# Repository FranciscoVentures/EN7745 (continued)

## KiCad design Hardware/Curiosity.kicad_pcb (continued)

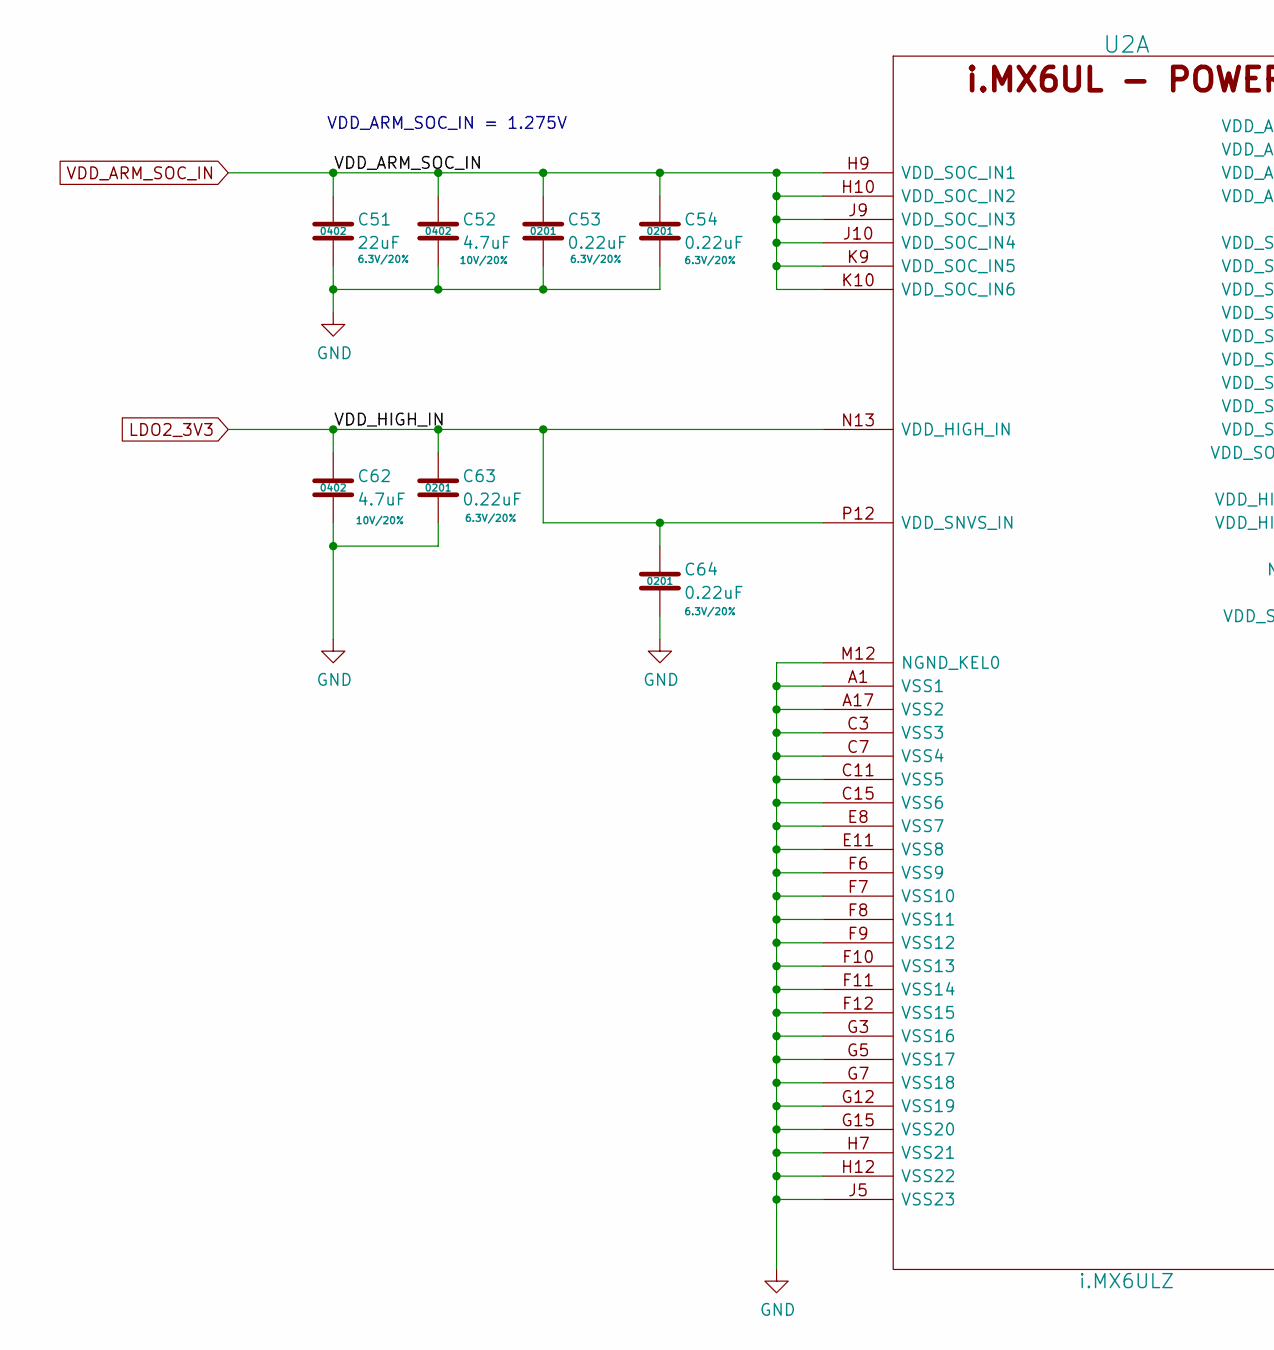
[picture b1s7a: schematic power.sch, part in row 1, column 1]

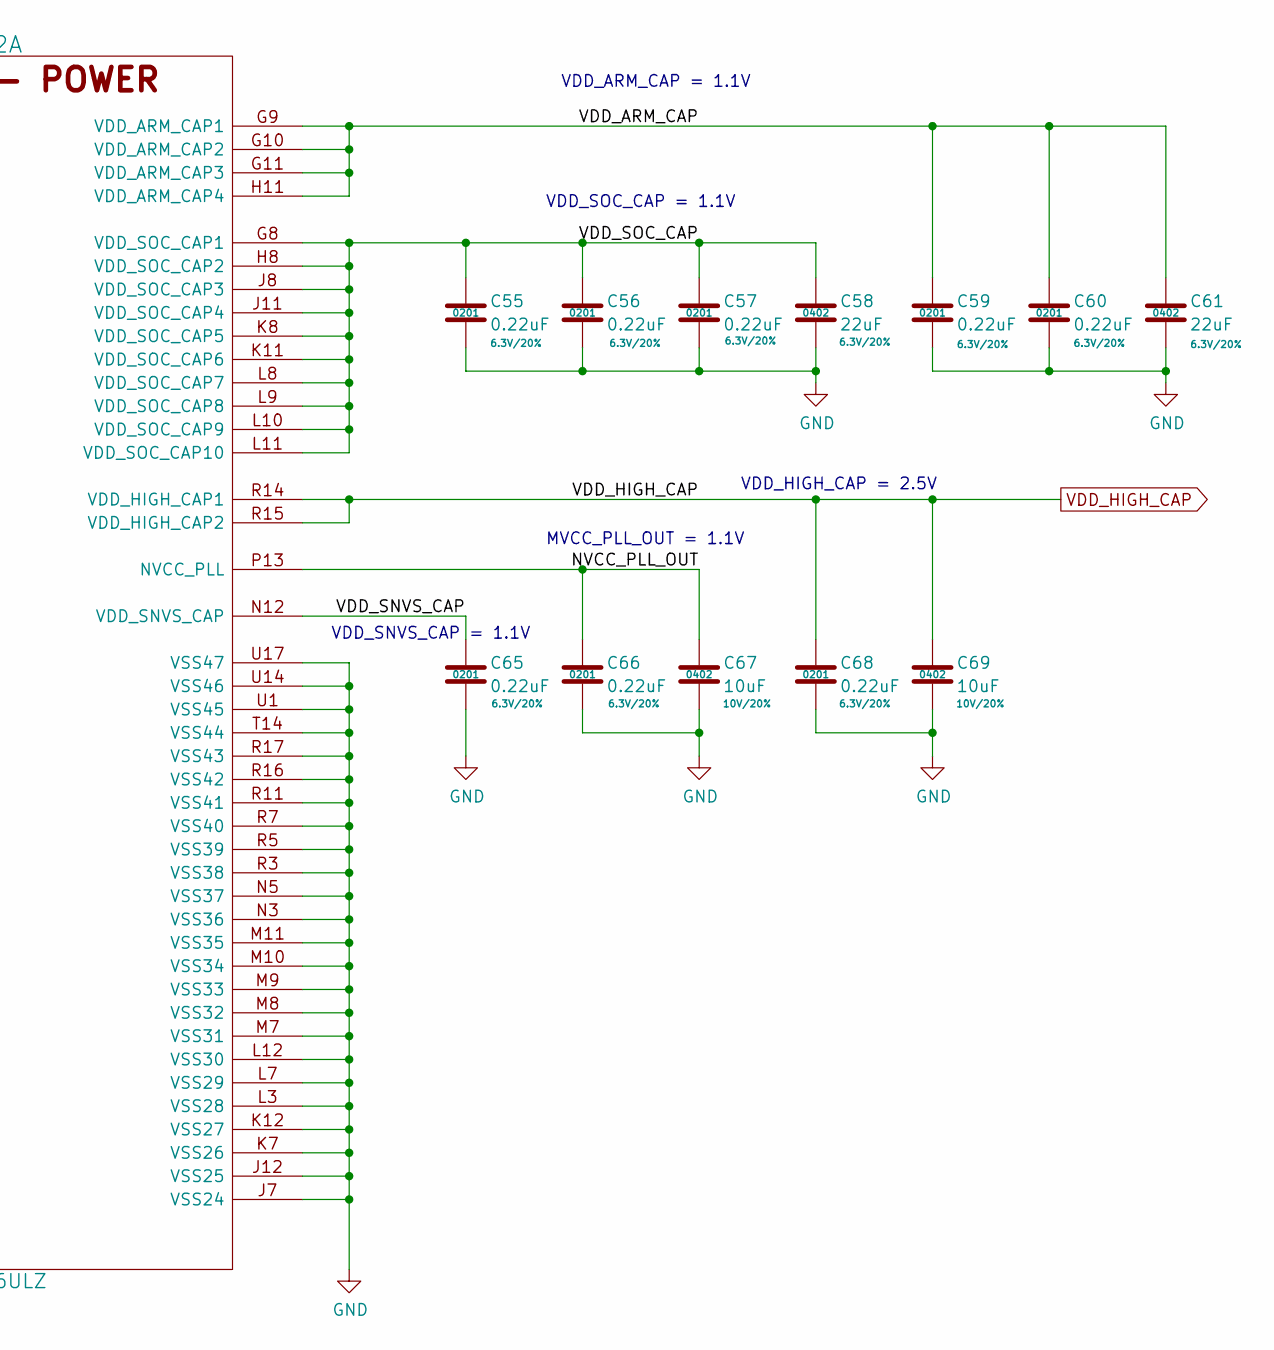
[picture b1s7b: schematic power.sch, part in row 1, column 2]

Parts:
C51, C58, C61: 22uF; SM0402; Rating 6.3V/20%; Mfg PN CL05A226MQ5N6J8; Digi-Key_PN 1276-7090-1-ND
C52, C62: 4.7uF; SM0402; Rating 10V/20%; Mfg PN ZRB15XR61A475ME01D; Digi-Key_PN 490-10984-1-ND
C53, C54, C55, C56, C57, C59, C60, C63, C64, C65, C66, C68: 0.22uF; SM0201; Rating 6.3V/20%; Mfg PN GRM033R60J224ME15D; Digi-Key_PN 490-10407-1-ND
C67, C69: 10uF; SM0402; Rating 10V/20%; Mfg PN CL05A106MP8NUB8; Digi-Key_PN 1276-6830-1-ND
U2: i.MX6ULZ; SOT1534-2; Mfg PN MCIMX6Z0DVM09AB; Digi-Key_PN 568-14726-ND

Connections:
/Power/NVCC_PLL_OUT: C66.1, C67.1, U2.P13 (NVCC_PLL); also elsewhere on the board
/Power/VDD_ARM_CAP: C59.1, C60.1, C61.1, U2.G9 (VDD_ARM_CAP1), U2.G10 (VDD_ARM_CAP2), U2.G11 (VDD_ARM_CAP3), U2.H11 (VDD_ARM_CAP4); also elsewhere on the board
/Power/VDD_SNVS_CAP: C65.1, U2.N12 (VDD_SNVS_CAP); also elsewhere on the board
/Power/VDD_SOC_CAP: C55.1, C56.1, C57.1, C58.1, U2.G8 (VDD_SOC_CAP1), U2.H8 (VDD_SOC_CAP2), U2.J8 (VDD_SOC_CAP3), U2.J11 (VDD_SOC_CAP4), U2.K8 (VDD_SOC_CAP5), U2.K11 (VDD_SOC_CAP6), U2.L8 (VDD_SOC_CAP7), U2.L9 (VDD_SOC_CAP8), U2.L10 (VDD_SOC_CAP9), U2.L11 (VDD_SOC_CAP10); also elsewhere on the board
GND: C51.2, C52.2, C53.2, C54.2, C55.2, C56.2, C57.2, C58.2, C59.2, C60.2, C61.2, C62.2, C63.2, C64.2, C65.2, C66.2, C67.2, C68.2, C69.2, U2.A1 (VSS1), U2.A17 (VSS2), U2.C3 (VSS3), U2.C7 (VSS4), U2.C11 (VSS5), U2.C15 (VSS6), U2.E8 (VSS7), U2.E11 (VSS8), U2.F6 (VSS9), U2.F7 (VSS10), U2.F8 (VSS11), U2.F9 (VSS12), U2.F10 (VSS13), U2.F11 (VSS14), U2.F12 (VSS15), U2.G3 (VSS16), U2.G5 (VSS17), U2.G7 (VSS18), U2.G12 (VSS19), U2.G15 (VSS20), U2.H7 (VSS21), U2.H12 (VSS22), U2.J5 (VSS23), U2.J7 (VSS24), U2.J12 (VSS25), U2.K7 (VSS26), U2.K12 (VSS27), U2.L3 (VSS28), U2.L7 (VSS29), U2.L12 (VSS30), U2.M7 (VSS31), U2.M8 (VSS32), U2.M9 (VSS33), U2.M10 (VSS34), U2.M11 (VSS35), U2.M12 (NGND_KEL0), U2.N3 (VSS36), U2.N5 (VSS37), U2.R3 (VSS38), U2.R5 (VSS39), U2.R7 (VSS40), U2.R11 (VSS41), U2.R16 (VSS42), U2.R17 (VSS43), U2.T14 (VSS44), U2.U1 (VSS45), U2.U14 (VSS46), U2.U17 (VSS47); also elsewhere on the board
LDO2_3V3: C62.1, C63.1, C64.1, U2.N13 (VDD_HIGH_IN), U2.P12 (VDD_SNVS_IN); also elsewhere on the board
VDD_ARM_SOC_IN: C51.1, C52.1, C53.1, C54.1, U2.H9 (VDD_SOC_IN1), U2.H10 (VDD_SOC_IN2), U2.J9 (VDD_SOC_IN3), U2.J10 (VDD_SOC_IN4), U2.K9 (VDD_SOC_IN5), U2.K10 (VDD_SOC_IN6); also elsewhere on the board
VDD_HIGH_CAP: C68.1, C69.1, U2.R14 (VDD_HIGH_CAP1), U2.R15 (VDD_HIGH_CAP2); also elsewhere on the board

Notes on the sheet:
VDD_ARM_SOC_IN = 1.275V
VDD_ARM_CAP = 1.1V
VDD_SOC_CAP = 1.1V
VDD_HIGH_CAP = 2.5V
MVCC_PLL_OUT = 1.1V
VDD_SNVS_CAP = 1.1V

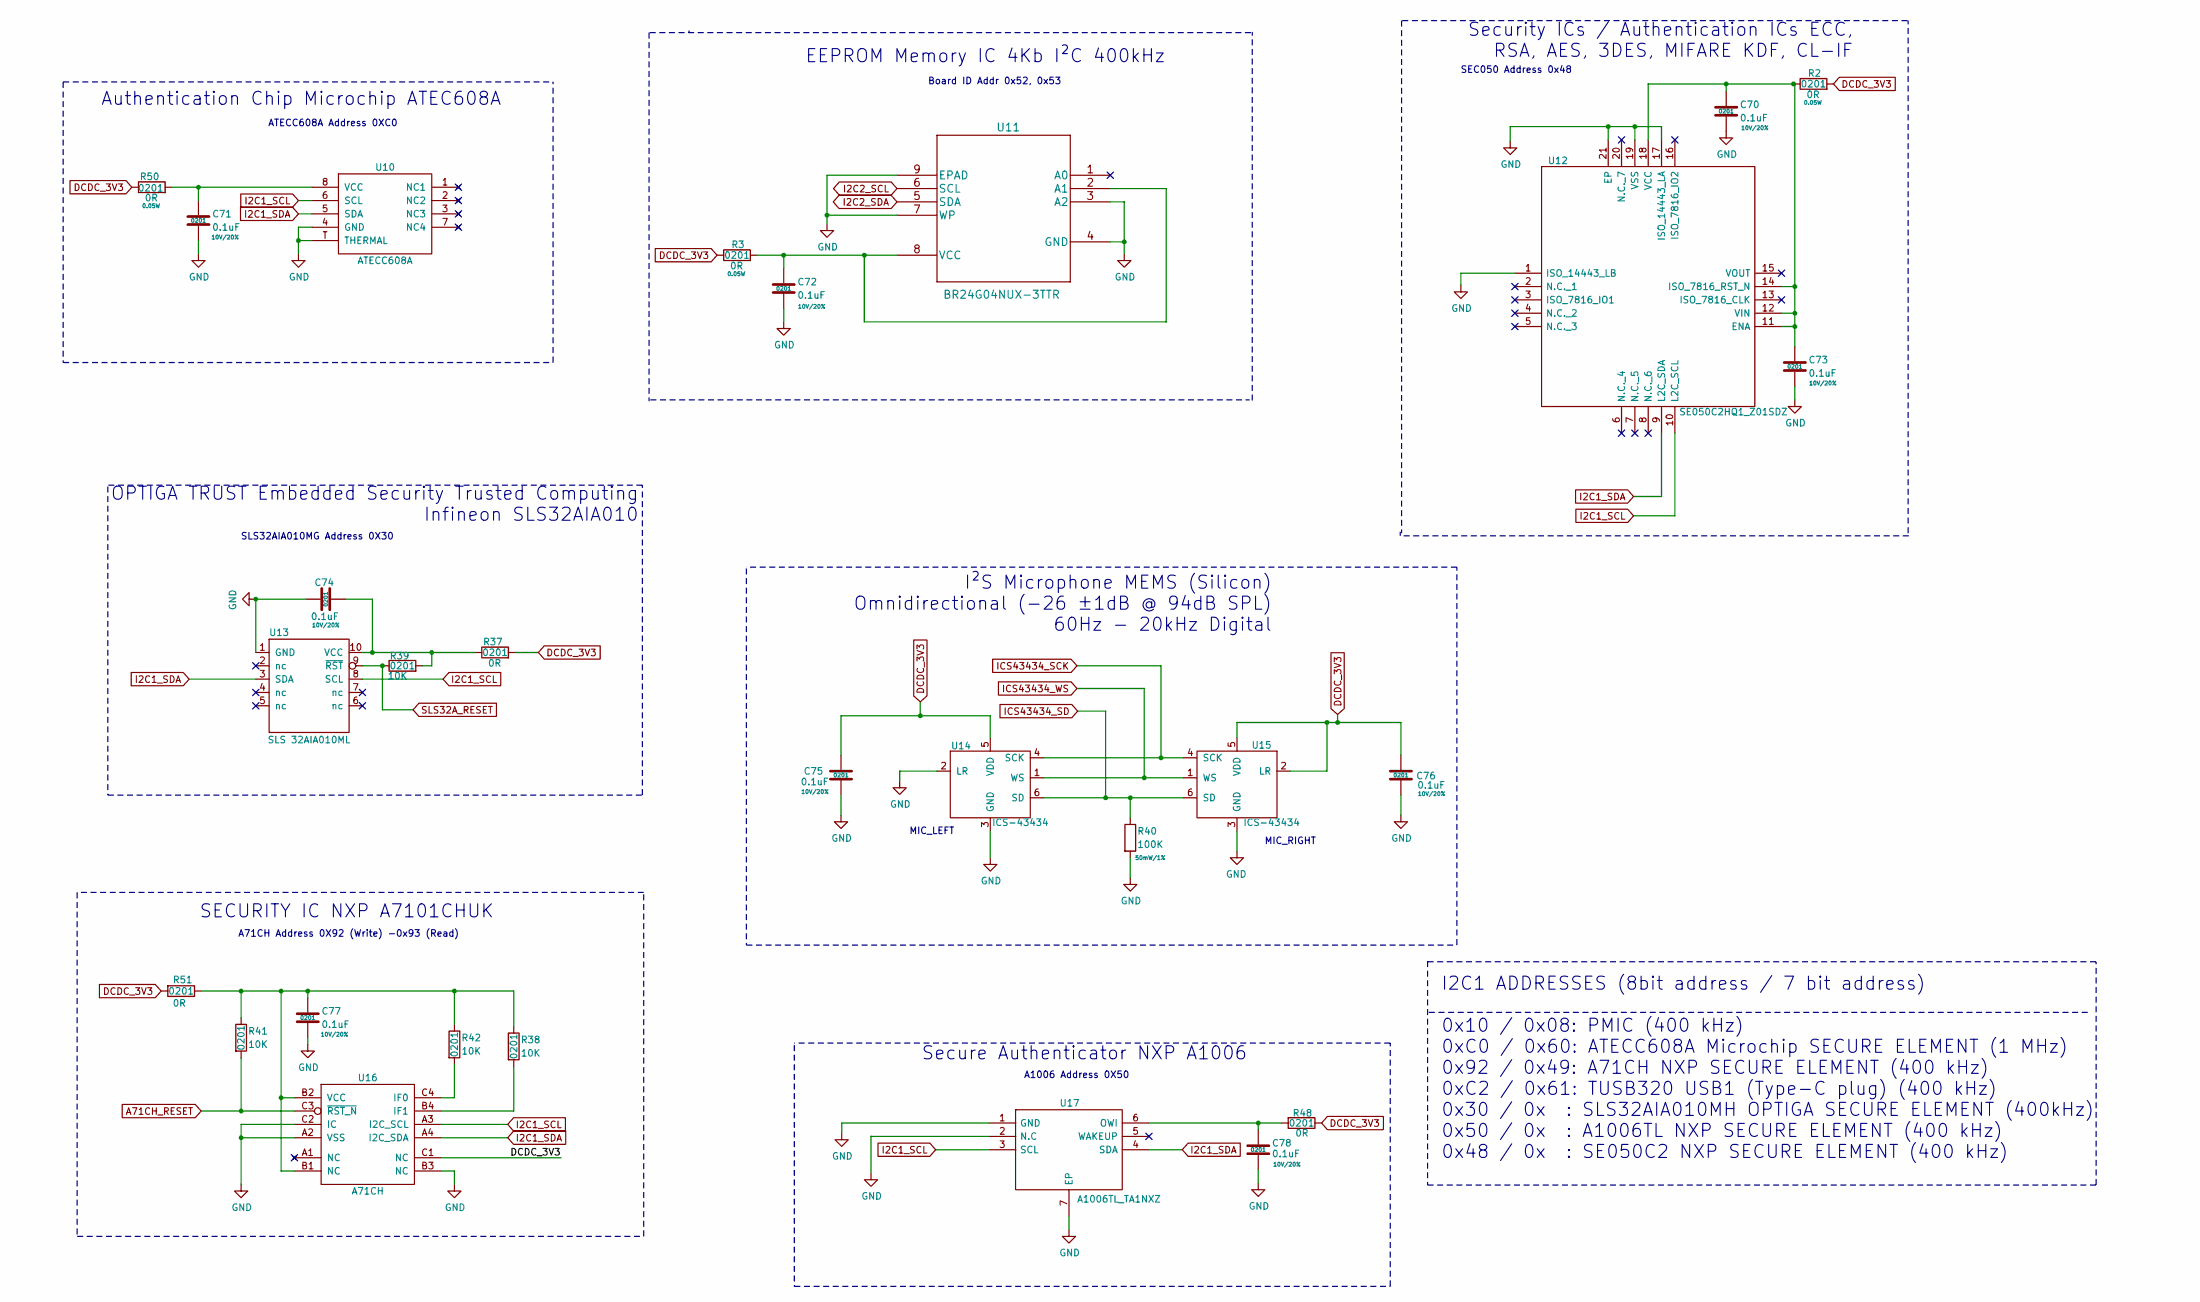
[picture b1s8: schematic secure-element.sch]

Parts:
C70, C71, C72, C73, C74, C75, C76, C77, C78: 0.1uF; SM0201; Rating 10V/20%; Mfg PN GRM033R61A104ME15D; Digi-Key_PN 490-5405-1-ND
R2, R3, R37, R50: 0R; R_0201_0603Metric; Rating 0.05W; Mfg PN CRCW02010000Z0ED; Digi-Key_PN 541-0.0AGCT-ND
R38, R39, R41, R42: 10K; R_0201_0603Metric; Rating 50mW/1%; Mfg PN CRCW020110K0JNED; Digi-Key_PN 541-10KAGCT-ND
R40: 100K; R_0201_0603Metric; Rating 50mW/1%; Mfg PN CRCW0201100KJNED; Digi-Key_PN 541-100KAGCT-ND
R48, R51: 0R; R_0201_0603Metric; Rating 50mW/1%; Mfg PN CRCW020110K0JNED; Digi-Key_PN 541-10KAGCT-ND
U10: ATECC608A; UDFN-8; Mfg PN ATECC608A-MAHDA; Digi-Key_PN ATECC608A-MAHDA-SCT-ND
U11: BR24G04NUX-3TTR; VSON008X2030_ROM; Mfg PN BR24G04NUX-3TTR; Digi-Key_PN BR24G04NUX-3TCT-ND
U12: SE050C2HQ1_Z01SDZ; QFN40P300X300X33-21N-D; Mfg PN SE050C2HQ1/Z01SDZ; Digi-Key_PN 568-15378-1-ND
U13: SLS 32AIA010ML; SLS; Mfg PN SLS32AIA010MH
U14, U15: ICS-43434; ICS43434; Mfg PN ICS-43434; Digi-Key_PN 1428-1066-1-ND
U16: A71CH; SOT1999-1; Mfg PN A7101CHUK/T0BC2HAZ; Digi-Key_PN 568-14698-1-ND
U17: A1006TL_TA1NXZ; SON65P200X200X50-7N; Mfg PN A1006TL/TA1NXZ; Digi-Key_PN 568-13635-1-ND

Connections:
A71CH_RESET: R41.2, U16.C3 (~RST_N); also elsewhere on the board
DCDC_3V3: C75.2, C76.2, R2.2, R3.1, R37.2, R48.1, R50.1, R51.2, U14.5 (VDD), U15.2 (LR), U15.5 (VDD), U16.C1 (NC); also elsewhere on the board
GND: C70.2, C71.2, C72.2, C73.2, C74.1, C75.1, C76.1, C77.2, C78.2, R40.2, U10.4 (GND), U10.T (THERMAL), U11.3 (A2), U11.4 (GND), U11.7 (WP), U11.9 (EPAD), U12.1 (ISO_14443_LB), U12.17 (ISO_14443_LA), U12.19 (VSS), U12.21 (EP), U13.1 (GND), U14.2 (LR), U14.3 (GND), U15.3 (GND), U16.A2 (VSS), U16.B3 (NC), U16.C2 (IC), U17.1 (GND), U17.2 (N.C), U17.7 (EP); also elsewhere on the board
I2C1_SCL: U10.6 (SCL), U12.10 (L2C_SCL), U13.8 (SCL), U16.A3 (I2C_SCL), U17.3 (SCL); also elsewhere on the board
I2C1_SDA: U10.5 (SDA), U12.9 (L2C_SDA), U13.3 (SDA), U16.A4 (I2C_SDA), U17.4 (SDA); also elsewhere on the board
I2C2_SCL: U11.6 (SCL); also elsewhere on the board
I2C2_SDA: U11.5 (SDA); also elsewhere on the board
ICS43434_SCK: U14.4 (SCK), U15.4 (SCK); also elsewhere on the board
ICS43434_SD: R40.1, U14.6 (SD), U15.6 (SD); also elsewhere on the board
ICS43434_WS: U14.1 (WS), U15.1 (WS); also elsewhere on the board
unnamed: C70.1, C73.1, R2.1, U12.11 (ENA), U12.12 (VIN), U12.14 (ISO_7816_RST_N), U12.18 (VCC)
unnamed: C71.1, R50.2, U10.8 (VCC)
unnamed: C72.1, R3.2, U11.2 (A1), U11.8 (VCC)
unnamed: C74.2, R37.1, R39.2, U13.10 (VCC)
unnamed: C77.1, R38.1, R41.1, R42.1, R51.1, U16.B1 (NC), U16.B2 (VCC)
unnamed: C78.1, R48.2, U17.6 (OWI)
unnamed: R38.2, U16.B4 (IF1)
unnamed: R42.2, U16.C4 (IF0)
SLS32A_RESET: R39.1, U13.9 (~RST); also elsewhere on the board

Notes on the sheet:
SLS32AIA010MG Address 0X30
A71CH Address 0X92 (Write) -0x93 (Read)
ATECC608A Address 0XC0
A1006 Address 0X50
SEC050 Address 0x48
Board ID Addr 0x52, 0x53
I2C1 ADDRESSES (8bit address / 7 bit address) 0x10 / 0x08: PMIC (400 kHz) 0xC0 / 0x60: ATECC608A Microchip SECURE ELEMENT (1 MHz) 0x92 / 0x49: A71CH NXP SECURE ELEMENT (400 kHz) 0xC2 / 0x61: TUSB320 USB1 (Type-C plug) (400 kHz) 0x30 / 0x : SLS32AIA010MH OPTIGA SECURE ELEMENT (400kHz) 0x50 / 0x : A1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
Secure Authenticator NXP A1006
I²S Microphone MEMS (Silicon) Omnidirectional (-26 ±1dB @ 94dB SPL) 60Hz - 20kHz Digital
Security ICs / Authentication ICs ECC, RSA, AES, 3DES, MIFARE KDF, CL-IF
EEPROM Memory IC 4Kb I²C 400kHz
OPTIGA TRUST Embedded Security Trusted Computing Infineon SLS32AIA010
SECURITY IC NXP A7101CHUK
Authentication Chip Microchip ATEC608A
MIC_RIGHT
MIC_LEFT

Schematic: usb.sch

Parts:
C21, C22, C26, C27: 0.1uF; SM0201; Rating 10V/20%; Mfg PN GRM033R61A104ME15D; Digi-Key_PN 490-5405-1-ND
C23: 1uF; SM0201; Rating 10V/20%; Mfg PN CL03A105MP3ZSNH; Digi-Key_PN 1276-6816-1-ND
C24: 0.1uF; SM0201; Rating 35V/10%; Mfg PN GRM033R6YA104KE14D; Digi-Key_PN 490-10430-1-ND
C25: 10uF; SM0402; Rating 10V/20%; Mfg PN CL05A106MP8NUB8; Digi-Key_PN 1276-6830-1-ND
C28: 4.7uF; SM0603; Rating 35V/10%; Mfg PN GRM188R6YA475KE15D; Digi-Key_PN 490-7205-1-ND
D1: NSR20F30NXT5G; DSN2; Rating 30V/2.0A/480mV@2A; Mfg PN NSR20F30NXT5G; Digi-Key_PN NSR20F30NXT5GOSCT-ND
J1: Debug Conn 8PIN; BC075-08; Mfg PN BC075-08-A-L-A; Digi-Key_PN 2073-BC075-08-A-L-ACT-ND
J2: USBC-PLUG; WURTH_632712000011; Mfg PN 632712000011; Digi-Key_PN 732-9616-1-ND
R24: 100K; R_0201_0603Metric; Rating 50mW/1%; Mfg PN CRCW0201100KJNED; Digi-Key_PN 541-100KAGCT-ND
R25: 1M; R_0201_0603Metric; Rating 50mW/1%; Mfg PN CRCW02011M00FKED; Digi-Key_PN 541-1.00MAABCT-ND
R26, R27: 10K; R_0201_0603Metric; Rating 50mW/1%; Mfg PN CRCW020110K0JNED; Digi-Key_PN 541-10KAGCT-ND
U2: i.MX6ULZ; SOT1534-2; Mfg PN MCIMX6Z0DVM09AB; Digi-Key_PN 568-14726-ND
U4: FPF2286UCX; WLCSP-6; Mfg PN FPF2286UCX; Digi-Key_PN FPF2286UCXOSCT-ND
U5: TPD8E003; WSON-8; Mfg PN TPD8E003DQDR; Digi-Key_PN 296-27669-1-ND
U6: TUSB320; RWB-QFN-12; Mfg PN TUSB320IRWBR; Digi-Key_PN 296-42175-1-ND
U7: TPD1E10B06; X1SON-2; Mfg PN TPD1E10B06DPYR; Digi-Key_PN 296-30406-1-ND
U8: TPD4E05U06-Q1; DQA-USON-10; Mfg PN TPD4E05U06DQAR; Digi-Key_PN 296-35765-1-ND

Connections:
/USB/USB1_CC: J2.A5 (CC), U6.1 (CC1), U8.4 (D2+), U8.7 (NC)
/USB/USB1_DN: J2.A7 (D-), U2.T15 (USB_OTG1_DN), U8.1 (D1+), U8.10 (NC); also elsewhere on the board
/USB/USB1_DP: J2.A6 (D+), U2.U15 (USB_OTG1_DP), U8.2 (D1-), U8.9 (NC); also elsewhere on the board
/USB/USB1_VBUS: C28.1, D1.2 (A), J2.A4 (VBUS), J2.A9 (VBUS), J2.B4 (VBUS), J2.B9 (VBUS), R24.1, R25.1, U7.1
/USB/USB_VBUS: C24.1, D1.1 (K), U4.A2 (IN), U4.B2 (IN)
/USB/VDD_USB_CAP: C25.1, C26.1, U2.R12 (VDD_USB_CAP); also elsewhere on the board
DCDC_3V3: C21.1, C27.1, J1.4, R26.1, R27.1, U6.12 (VDD); also elsewhere on the board
GND: C21.2, C22.2, C23.2, C24.2, C25.2, C26.2, C27.2, C28.2, J1.1, J2.A1 (GND), J2.A12 (GND), J2.B1 (GND), J2.B12 (GND), J2.S, R24.2, U4.C1 (GND), U4.C2 (OVLO), U5.GND, U6.3 (PORT), U6.10 (GND), U6.11 (EN_N), U7.2, U8.3 (GND), U8.8 (GND); also elsewhere on the board
GPIO1_IO25: J1.8, U5.7 (IO7); also elsewhere on the board
GPIO1_IO27: J1.7; also elsewhere on the board
I2C1_SCL: J1.6, U5.4 (IO4), U6.8 (SCL/OUT2); also elsewhere on the board
I2C1_SDA: J1.5, U5.3 (IO3), U6.7 (SDA/OUT1); also elsewhere on the board
unnamed: R25.2, U6.4 (VBUS_DET)
unnamed: R27.2, U6.5 (ADDR)
unnamed 233: U2.T13 (USB_OTG2_DN); also elsewhere on the board
unnamed 235: U2.U12 (USB_OTG2_VBUS); also elsewhere on the board
unnamed 236: U2.U13 (USB_OTG2_DP); also elsewhere on the board
unnamed 237: U2.U16 (~USB_OTG1_CHD); also elsewhere on the board
UART4_RX: J1.3, U5.2 (IO2); also elsewhere on the board
UART4_TX: J1.2, U5.1 (IO1); also elsewhere on the board
USB1_INT_B: R26.2, U6.6 (INT_N/OUT3); also elsewhere on the board
VSYS_5V: C22.1, C23.1, U2.T12 (USB_OTG1_VBUS), U4.A1 (OUT), U4.B1 (OUT); also elsewhere on the board

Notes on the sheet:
ADDR pulled-up: 0xC2 I2C address selected. PORT tied to GND: UFP mode selected.
TUSB320 device is used to support the USB Type-C Current feature The Source can advertise to the Sink the amount of current it can supply: - Default (500 mA for USB 2.0 or 900 mA for USB 3.1) - USB Type-C Current @ 1.5 A - USB Type-C Current @ 3.0 A
USB 2.0 Type-C plug
Type-C plug ESD protection
Connector ESD protection
Type-C plug port controller - UFP MODE
OVP Voltage = 6.8V
5V, 500mA -> R=35mOhm V_drop(3A) = 100mV
Over voltage protection
i.MX6UL USB interface
R33 required to keep USB1_VBUS low from 2.2V to 0.4V
Debug Connector 8 Pin

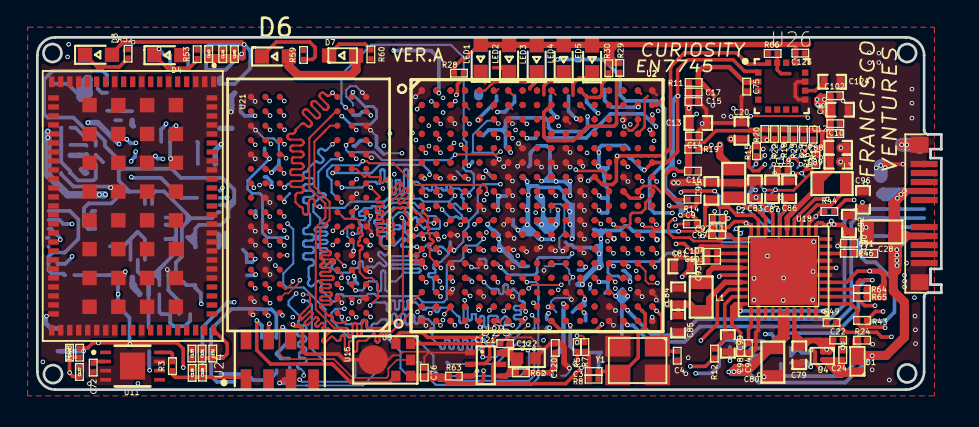
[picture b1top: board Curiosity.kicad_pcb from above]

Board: 8 copper layers, 50.2 x 19.6 mm, 234 parts (0 on the bottom side), 247 nets.

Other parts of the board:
C108, C110, C126, C127, C128, C129, C130, C131, C132, C133: 0.1uF; SM0201
U2#2: i.MX6ULZ; SOT1534-2
U21: G313-06329-00; G3130632900

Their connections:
/Boot/BT_CFG1[0]: U2#2.B9; also elsewhere on the board
/Boot/BT_CFG1[1]: U2#2.A9; also elsewhere on the board
/Boot/BT_CFG1[2]: U2#2.E10; also elsewhere on the board
/Boot/BT_CFG1[3]: U2#2.D10; also elsewhere on the board
/Boot/BT_CFG1[4]: U2#2.C10; also elsewhere on the board
/Boot/BT_CFG1[5]: U2#2.B10, U2#2.D12; also elsewhere on the board
/Boot/BT_CFG1[6]: U2#2.A10; also elsewhere on the board
/Boot/BT_CFG1[7]: U2#2.D11; also elsewhere on the board
/Boot/BT_CFG2[0]: U2#2.B11; also elsewhere on the board
/Boot/BT_CFG2[1]: U2#2.A11; also elsewhere on the board
/Boot/BT_CFG2[2]: U2#2.E12; also elsewhere on the board
/Boot/BT_CFG2[4]: U2#2.C12; also elsewhere on the board
/Boot/BT_CFG2[5]: U2#2.B12; also elsewhere on the board
/Boot/BT_CFG2[6]: U2#2.A12; also elsewhere on the board
/Boot/BT_CFG2[7]: U2#2.D13; also elsewhere on the board
/Boot/BT_CFG4[0]: U2#2.C13; also elsewhere on the board
/Boot/BT_CFG4[1]: U2#2.B13; also elsewhere on the board
/Boot/BT_CFG4[2]: U2#2.A13; also elsewhere on the board
/Boot/BT_CFG4[3]: U2#2.D14; also elsewhere on the board
/Boot/BT_CFG4[4]: U2#2.C14; also elsewhere on the board
/Boot/BT_CFG4[5]: U2#2.B14; also elsewhere on the board
/Boot/BT_CFG4[6]: U2#2.A14; also elsewhere on the board
/Boot/BT_CFG4[7]: U2#2.B16; also elsewhere on the board
/Crystals/BOOT_MODE0: U2#2.T10; also elsewhere on the board
/Crystals/BOOT_MODE1: U2#2.U10; also elsewhere on the board
/Crystals/JTAG_MOD: U2#2.P15; also elsewhere on the board
/Crystals/JTAG_TCK: U2#2.M14; also elsewhere on the board
/Crystals/JTAG_TDI: U2#2.N16; also elsewhere on the board
/Crystals/JTAG_TDO: U2#2.N15; also elsewhere on the board
/Crystals/JTAG_TMS: U2#2.P14; also elsewhere on the board
/Crystals/JTAG_nSRST: U2#2.P8; also elsewhere on the board
/Crystals/JTAG_nTRST: U2#2.N14; also elsewhere on the board
/Crystals/RTC_XTALI: U2#2.T11; also elsewhere on the board
/Crystals/RTC_XTALO: U2#2.U11; also elsewhere on the board
/Crystals/XTALI: U2#2.T16; also elsewhere on the board
/Crystals/XTALO: U2#2.T17; also elsewhere on the board
/DDR/DRAM_A0: U2#2.L5; also elsewhere on the board
/DDR/DRAM_A1: U2#2.H2; also elsewhere on the board
/DDR/DRAM_A2: U2#2.K1; also elsewhere on the board
/DDR/DRAM_A3: U2#2.M2; also elsewhere on the board
/DDR/DRAM_A4: U2#2.K4; also elsewhere on the board
/DDR/DRAM_A5: U2#2.L1; also elsewhere on the board
/DDR/DRAM_A6: U2#2.G2; also elsewhere on the board
/DDR/DRAM_A7: U2#2.H4; also elsewhere on the board
/DDR/DRAM_A8: U2#2.J4; also elsewhere on the board
/DDR/DRAM_A9: U2#2.L2; also elsewhere on the board
/DDR/DRAM_A10: U2#2.M4; also elsewhere on the board
/DDR/DRAM_A11: U2#2.K3; also elsewhere on the board
/DDR/DRAM_A12: U2#2.L4; also elsewhere on the board
/DDR/DRAM_A13: U2#2.H3; also elsewhere on the board
/DDR/DRAM_A14: U2#2.G1; also elsewhere on the board
/DDR/DRAM_A15: U2#2.K5; also elsewhere on the board
/DDR/DRAM_CAS_B: U2#2.J2; also elsewhere on the board
/DDR/DRAM_CS0_B: U2#2.N2; also elsewhere on the board
/DDR/DRAM_D0: U2#2.T4; also elsewhere on the board
/DDR/DRAM_D1: U2#2.U6; also elsewhere on the board
/DDR/DRAM_D2: U2#2.T6; also elsewhere on the board
/DDR/DRAM_D3: U2#2.U7; also elsewhere on the board
/DDR/DRAM_D4: U2#2.U8; also elsewhere on the board
/DDR/DRAM_D5: U2#2.T8; also elsewhere on the board
/DDR/DRAM_D6: U2#2.T5; also elsewhere on the board
/DDR/DRAM_D7: U2#2.U4; also elsewhere on the board
/DDR/DRAM_D8: U2#2.U2; also elsewhere on the board
/DDR/DRAM_D9: U2#2.U3; also elsewhere on the board
/DDR/DRAM_D10: U2#2.U5; also elsewhere on the board
/DDR/DRAM_D11: U2#2.R4; also elsewhere on the board
/DDR/DRAM_D12: U2#2.P5; also elsewhere on the board
/DDR/DRAM_D13: U2#2.P3; also elsewhere on the board
/DDR/DRAM_D14: U2#2.R2; also elsewhere on the board
/DDR/DRAM_D15: U2#2.R1; also elsewhere on the board
/DDR/DRAM_DQM0: U2#2.T7; also elsewhere on the board
/DDR/DRAM_DQM1: U2#2.T3; also elsewhere on the board
/DDR/DRAM_RAS_B: U2#2.M5; also elsewhere on the board
/DDR/DRAM_RESET_B: U2#2.G4; also elsewhere on the board
/DDR/DRAM_SDBA0: U2#2.M1; also elsewhere on the board
/DDR/DRAM_SDBA1: U2#2.H1; also elsewhere on the board
/DDR/DRAM_SDBA2: U2#2.K2; also elsewhere on the board
/DDR/DRAM_SDCKE0: U2#2.M3; also elsewhere on the board
/DDR/DRAM_SDCLK0_N: U2#2.P2; also elsewhere on the board
/DDR/DRAM_SDCLK0_P: U2#2.P1; also elsewhere on the board
/DDR/DRAM_SDODT0: U2#2.N1; also elsewhere on the board
/DDR/DRAM_SDQS0_N: U2#2.P7; also elsewhere on the board
/DDR/DRAM_SDQS0_P: U2#2.P6; also elsewhere on the board
/DDR/DRAM_SDQS1_N: U2#2.T2; also elsewhere on the board
/DDR/DRAM_SDQS1_P: U2#2.T1; also elsewhere on the board
/DDR/DRAM_WE_B: U2#2.J1; also elsewhere on the board
/DDR/DRAM_ZQPAD: U2#2.N4; also elsewhere on the board
/Power/NVCC_PLL_OUT: U2#2.P13; also elsewhere on the board
/Power/VDD_ARM_CAP: U2#2.G9, U2#2.G10, U2#2.G11, U2#2.H11; also elsewhere on the board
/Power/VDD_SNVS_CAP: U2#2.N12; also elsewhere on the board
/Power/VDD_SOC_CAP: U2#2.G8, U2#2.H8, U2#2.J8, U2#2.J11, U2#2.K8, U2#2.K11, U2#2.L8, U2#2.L9, U2#2.L10, U2#2.L11; also elsewhere on the board
/USB/USB1_DN: U2#2.T15; also elsewhere on the board
/USB/USB1_DP: U2#2.U15; also elsewhere on the board
/USB/VDD_USB_CAP: U2#2.R12; also elsewhere on the board
/eMMC/SD2_CLK_R: U2#2.D8; also elsewhere on the board
/eMMC/SD2_CMD: U2#2.C8; also elsewhere on the board
/eMMC/SD2_DATA0: U2#2.D7; also elsewhere on the board
/eMMC/SD2_DATA1: U2#2.B7; also elsewhere on the board
/eMMC/SD2_DATA2: U2#2.A7; also elsewhere on the board
/eMMC/SD2_DATA3: U2#2.D6; also elsewhere on the board
/eMMC/SD2_DATA4: U2#2.C6; also elsewhere on the board
/eMMC/SD2_DATA5: U2#2.B6; also elsewhere on the board
/eMMC/SD2_DATA6: U2#2.A6; also elsewhere on the board
/eMMC/SD2_DATA7: U2#2.A5; also elsewhere on the board
/eMMC/SD2_RESET_B: U2#2.B4; also elsewhere on the board
A71CH_RESET: U2#2.A16; also elsewhere on the board
Amb_sensor_INT: U2#2.M17; also elsewhere on the board
DCDC_3V3: C108.1, C110.1, C126.1, C127.1, C128.1, C129.1, C130.1, C131.1, C132.1, U2#2.C4, U2#2.E13, U2#2.F4, U2#2.F13, U2#2.H13, U2#2.J13, U21.56, U21.57, U21.58, U21.59, U21.60, U21.61, U21.62, U21.63, U21.64, U21.65, U21.66, U21.67; also elsewhere on the board
DDR_1V35: U2#2.G6, U2#2.H6, U2#2.J6, U2#2.K6, U2#2.L6, U2#2.M6; also elsewhere on the board
DDR_VREF: U2#2.P4; also elsewhere on the board
GND: C108.2, C110.2, C126.2, C127.2, C128.2, C129.2, C130.2, C131.2, C132.2, C133.2, U2#2.A1, U2#2.A17, U2#2.C3, U2#2.C7, U2#2.C11, U2#2.C15, U2#2.E8, U2#2.E11, U2#2.F6, U2#2.F7, U2#2.F8, U2#2.F9, U2#2.F10, U2#2.F11, U2#2.F12, U2#2.G3, U2#2.G5, U2#2.G7, U2#2.G12, U2#2.G15, U2#2.H7, U2#2.H12, U2#2.J5, U2#2.J7, U2#2.J12, U2#2.K7, U2#2.K12, U2#2.L3, U2#2.L7, U2#2.L12, U2#2.M7, U2#2.M8, U2#2.M9, U2#2.M10, U2#2.M11, U2#2.M12, U2#2.N3, U2#2.N5, U2#2.N7, U2#2.R3, U2#2.R5, U2#2.R7, U2#2.R11, U2#2.R16, U2#2.R17, U2#2.T14, U2#2.U1, U2#2.U14, U2#2.U17, U21.1, U21.2, U21.3, U21.6, U21.9, U21.12, U21.15, U21.16, U21.17, U21.18, U21.19, U21.20, U21.21, U21.22, U21.23, U21.24, U21.25, U21.26, U21.27, U21.28, U21.29, U21.30, U21.31, U21.32, U21.33, U21.34, U21.35, U21.36, U21.38, U21.39, U21.40, U21.41, U21.42, U21.43, U21.44, U21.45, U21.46, U21.47, U21.48, U21.49, U21.50, U21.51, U21.52, U21.55, U21.68, U21.69, U21.70, U21.71, U21.72, U21.73, U21.74, U21.75, U21.79, U21.80, U21.81, U21.84, U21.85, U21.86, U21.87, U21.88; also elsewhere on the board
GPIO1_IO25: U2#2.H15; also elsewhere on the board
GPIO1_IO27: U2#2.G14; also elsewhere on the board
GPS_PIO14: U2#2.D16, U21.53; also elsewhere on the board
GPS_RESET: U2#2.C16, U21.76; also elsewhere on the board
GPS_SAFEBOOT_N: U2#2.D17; also elsewhere on the board
GPS_UART_RX: U2#2.H16; also elsewhere on the board
GPS_UART_TX: U2#2.H17; also elsewhere on the board
I2C1_SCL: U2#2.L14; also elsewhere on the board
I2C1_SDA: U2#2.L17; also elsewhere on the board
I2C2_SCL: U2#2.F17; also elsewhere on the board
I2C2_SDA: U2#2.G13; also elsewhere on the board
ICS43434_SCK: U2#2.E1; also elsewhere on the board
ICS43434_SD: U2#2.D2; also elsewhere on the board
ICS43434_WS: U2#2.E2; also elsewhere on the board
LDO1_1V8: U21.54; also elsewhere on the board
LDO2_3V3: U2#2.L13, U2#2.M13, U2#2.N13, U2#2.P12; also elsewhere on the board
MPU6K_INT: U2#2.L15; also elsewhere on the board
NVCC_NAND: U2#2.E7; also elsewhere on the board
unnamed 172: U2#2.E4; also elsewhere on the board
unnamed 173: U2#2.E3; also elsewhere on the board
unnamed 174: U2#2.A2; also elsewhere on the board
unnamed 175: U2#2.A3; also elsewhere on the board
unnamed 176: U2#2.A4; also elsewhere on the board
unnamed 177: U2#2.A8; also elsewhere on the board
unnamed 178: U2#2.A15; also elsewhere on the board
unnamed 179: U2#2.B1; also elsewhere on the board
unnamed 180: U2#2.B2; also elsewhere on the board
unnamed 181: U2#2.B3; also elsewhere on the board
unnamed 182: U2#2.B5; also elsewhere on the board
unnamed 183: U2#2.B8; also elsewhere on the board
unnamed 184: U2#2.B15; also elsewhere on the board
unnamed 185: U2#2.C1; also elsewhere on the board
unnamed 186: U2#2.C2; also elsewhere on the board
unnamed 187: U2#2.C5; also elsewhere on the board
unnamed 188: U2#2.C9; also elsewhere on the board
unnamed 189: U2#2.D1; also elsewhere on the board
unnamed 190: U2#2.D3; also elsewhere on the board
unnamed 191: U2#2.D4; also elsewhere on the board
unnamed 192: U2#2.D5; also elsewhere on the board
unnamed 193: U2#2.D9; also elsewhere on the board
unnamed 194: U2#2.D15; also elsewhere on the board
unnamed 195: U2#2.E5; also elsewhere on the board
unnamed 196: U2#2.E6; also elsewhere on the board
unnamed 197: U2#2.E9; also elsewhere on the board
unnamed 198: U2#2.E14; also elsewhere on the board
unnamed 199: U2#2.E15; also elsewhere on the board
unnamed 200: U2#2.E16; also elsewhere on the board
unnamed 201: U2#2.E17; also elsewhere on the board
unnamed 202: U2#2.F1; also elsewhere on the board
unnamed 203: U2#2.F2; also elsewhere on the board
unnamed 204: U2#2.F3; also elsewhere on the board
unnamed 205: U2#2.F5; also elsewhere on the board
unnamed 206: U2#2.F14; also elsewhere on the board
unnamed 207: U2#2.F16; also elsewhere on the board
unnamed 208: U2#2.H5; also elsewhere on the board
unnamed 209: U2#2.H14; also elsewhere on the board
unnamed 210: U2#2.J3; also elsewhere on the board
unnamed 211: U2#2.J14; also elsewhere on the board
unnamed 212: U2#2.J15; also elsewhere on the board
unnamed 213: U2#2.J16; also elsewhere on the board
unnamed 214: U2#2.J17; also elsewhere on the board
unnamed 215: U2#2.K14; also elsewhere on the board
unnamed 216: U2#2.K15; also elsewhere on the board
unnamed 217: U2#2.K16; also elsewhere on the board
unnamed 218: U2#2.N8; also elsewhere on the board
unnamed 219: U2#2.N9; also elsewhere on the board
unnamed 220: U2#2.N10; also elsewhere on the board
unnamed 221: U2#2.N11; also elsewhere on the board
unnamed 222: U2#2.P9; also elsewhere on the board
unnamed 223: U2#2.P10; also elsewhere on the board
unnamed 224: U2#2.P11; also elsewhere on the board
unnamed 225: U2#2.P16; also elsewhere on the board
unnamed 226: U2#2.P17; also elsewhere on the board
unnamed 227: U2#2.R6; also elsewhere on the board
unnamed 228: U2#2.R8; also elsewhere on the board
unnamed 229: U2#2.R9; also elsewhere on the board
unnamed 230: U2#2.R10; also elsewhere on the board
unnamed 231: U2#2.R13; also elsewhere on the board
unnamed 232: U2#2.T9; also elsewhere on the board
unnamed 233: U2#2.T13; also elsewhere on the board
unnamed 234: U2#2.U9; also elsewhere on the board
unnamed 235: U2#2.U12; also elsewhere on the board
unnamed 236: U2#2.U13; also elsewhere on the board
unnamed 237: U2#2.U16; also elsewhere on the board
PMIC_WDI: U2#2.F15; also elsewhere on the board
SE1_LED: U2#2.M15; also elsewhere on the board
SE2_LED: U2#2.N17; also elsewhere on the board
SE3_LED: U2#2.L16; also elsewhere on the board
SE4_LED: U2#2.K17; also elsewhere on the board
SE5_LED: U2#2.M16; also elsewhere on the board
SLS32A_RESET: U2#2.C17; also elsewhere on the board
UART4_RX: U2#2.G16; also elsewhere on the board
UART4_TX: U2#2.G17; also elsewhere on the board
USB1_INT_B: U2#2.K13; also elsewhere on the board
VDD_ARM_SOC_IN: U2#2.H9, U2#2.H10, U2#2.J9, U2#2.J10, U2#2.K9, U2#2.K10; also elsewhere on the board
VDD_HIGH_CAP: U2#2.N6, U2#2.R14, U2#2.R15; also elsewhere on the board
VSYS_5V: U2#2.T12; also elsewhere on the board
eCompass_INT: U2#2.B17; also elsewhere on the board

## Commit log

2021-01-12 changes the copyright
2021-01-12 modified readme
